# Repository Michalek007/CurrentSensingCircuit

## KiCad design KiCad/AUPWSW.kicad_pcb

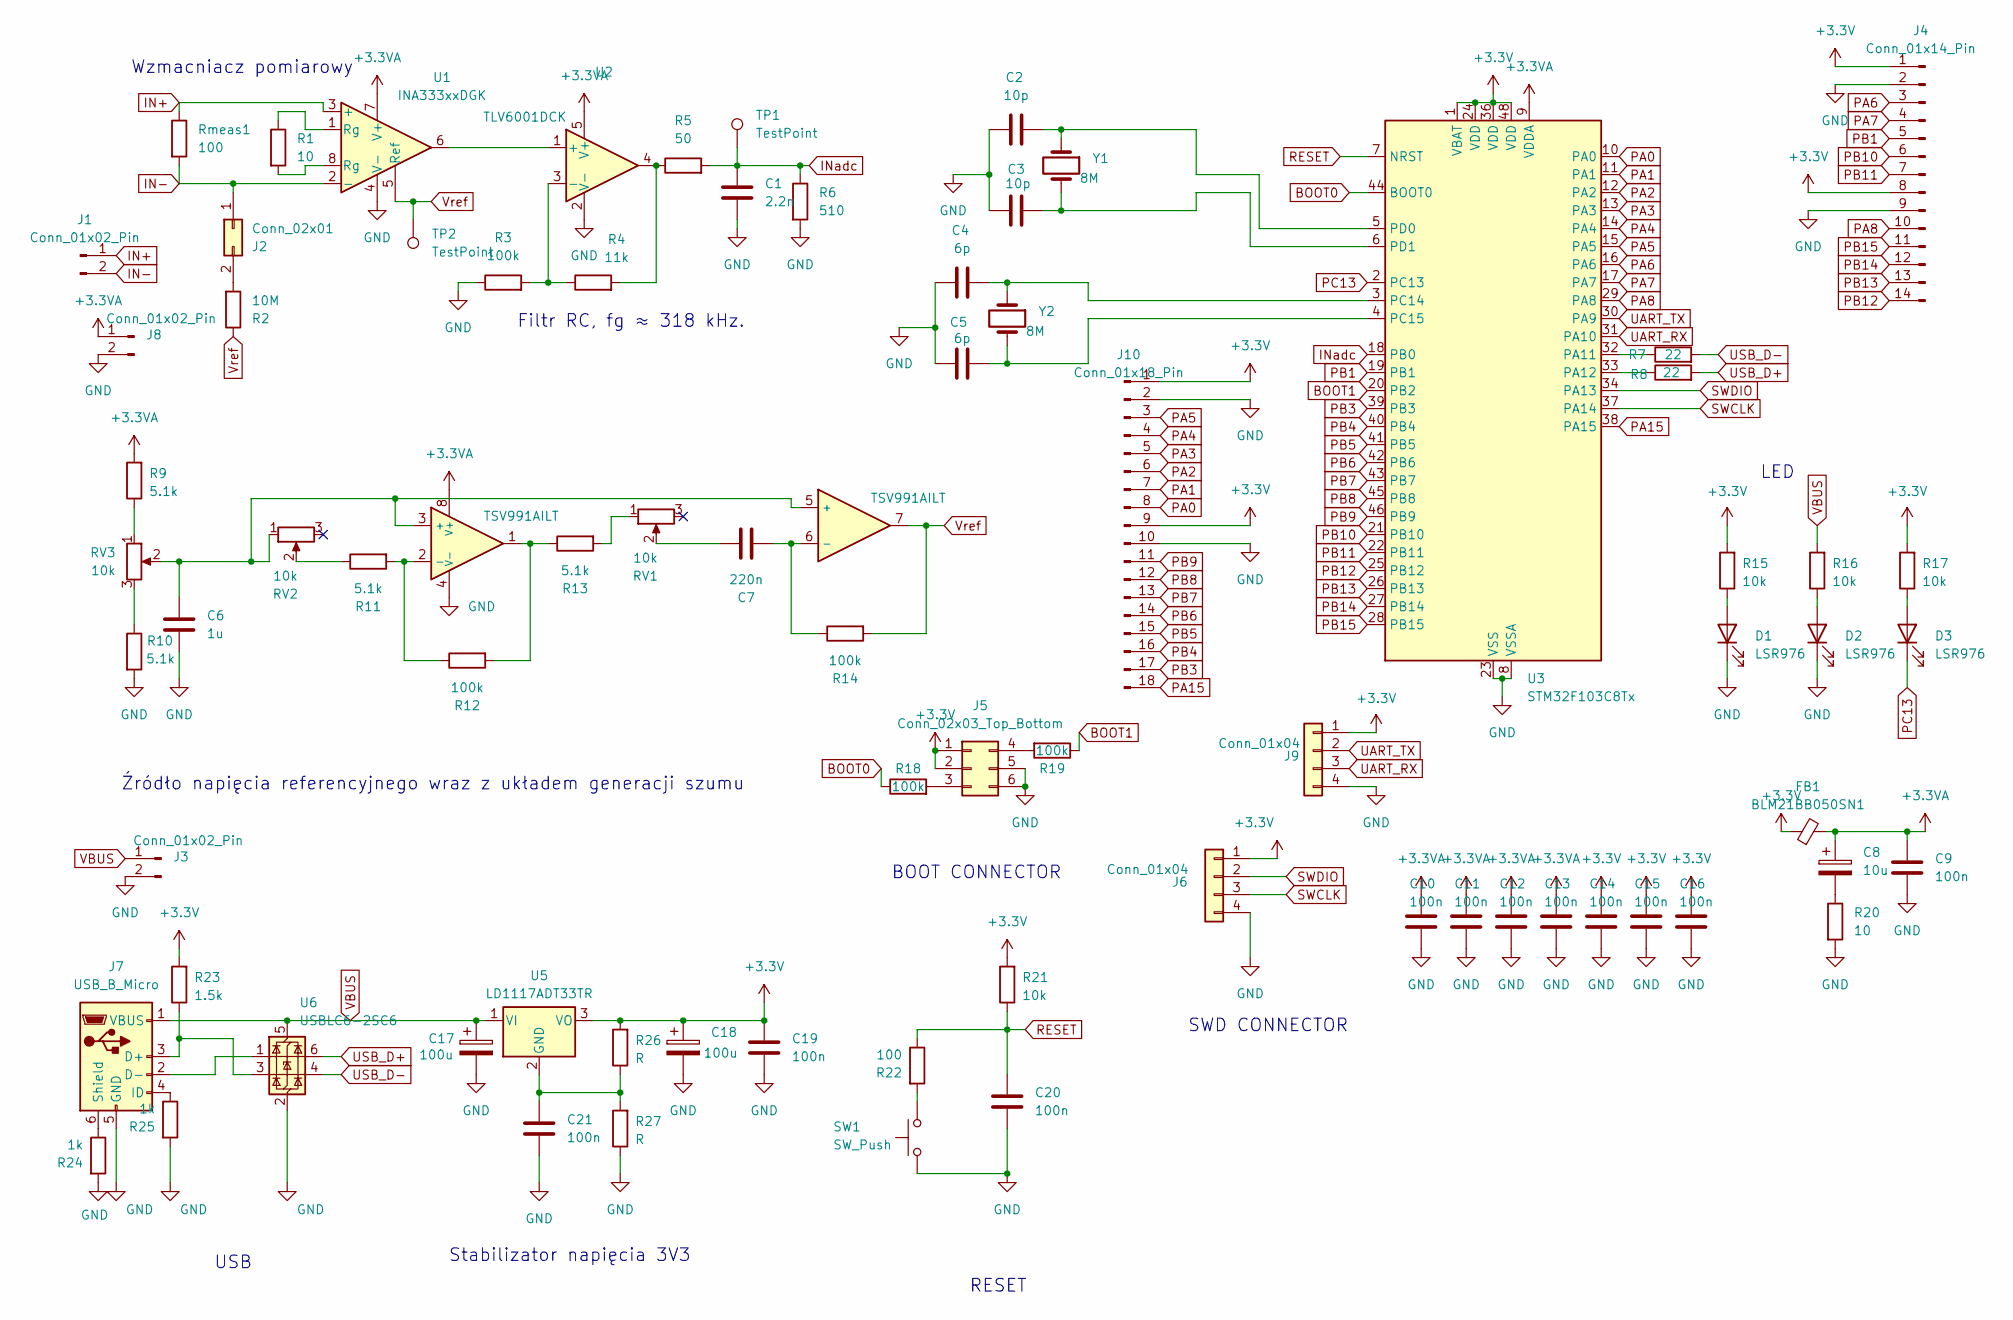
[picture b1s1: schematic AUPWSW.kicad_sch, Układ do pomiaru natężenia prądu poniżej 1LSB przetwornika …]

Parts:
C1: 2.2n; C_0805_2012Metric_Pad1.18x1.45mm_HandSolder
C2, C3: 10p; C_0603_1608Metric_Pad1.08x0.95mm_HandSolder
C4, C5: 6p; C_0603_1608Metric_Pad1.08x0.95mm_HandSolder
C6: 1u; C_0805_2012Metric_Pad1.18x1.45mm_HandSolder
C7: 220n; C_0805_2012Metric_Pad1.18x1.45mm_HandSolder
C8: 10u; CP_Elec_5x3
C9, C10, C11, C12, C13, C14, C15, C16, C19, C20, C21: 100n; C_0805_2012Metric_Pad1.18x1.45mm_HandSolder
C17, C18: 100u; CP_Elec_6.3x3
D1, D2, D3: LSR976; LED_0805_2012Metric_Pad1.15x1.40mm_HandSolder
FB1: BLM21BB050SN1; R_0805_2012Metric_Pad1.20x1.40mm_HandSolder
J1, J3, J8: Conn_01x02_Pin; PinHeader_1x02_P2.54mm_Vertical
J2: Conn_02x01; PinHeader_1x02_P2.54mm_Vertical
J4: Conn_01x14_Pin; PinHeader_1x14_P2.54mm_Vertical
J5: Conn_02x03_Top_Bottom; PinHeader_2x03_P2.54mm_Vertical
J6, J9: Conn_01x04; PinHeader_1x04_P2.54mm_Vertical
J7: USB_B_Micro; USB3080-30-00-A
J10: Conn_01x18_Pin; PinHeader_1x18_P2.54mm_Vertical
R1, R20: 10; R_0805_2012Metric_Pad1.20x1.40mm_HandSolder
R2: 10M; R_0805_2012Metric_Pad1.20x1.40mm_HandSolder
R3, R12, R14, R18, R19: 100k; R_0805_2012Metric_Pad1.20x1.40mm_HandSolder
R4: 11k; R_0805_2012Metric_Pad1.20x1.40mm_HandSolder
R5: 50; R_0805_2012Metric_Pad1.20x1.40mm_HandSolder
R6: 510; R_0805_2012Metric_Pad1.20x1.40mm_HandSolder
R7, R8: 22; R_0805_2012Metric_Pad1.20x1.40mm_HandSolder
R9, R10, R11, R13: 5.1k; R_0805_2012Metric_Pad1.20x1.40mm_HandSolder
R15, R16, R17, R21: 10k; R_0805_2012Metric_Pad1.20x1.40mm_HandSolder
R22: 100; R_0805_2012Metric_Pad1.20x1.40mm_HandSolder
R23: 1.5k; R_0805_2012Metric_Pad1.20x1.40mm_HandSolder
R24, R25: 1k; R_0805_2012Metric_Pad1.20x1.40mm_HandSolder
R26, R27: R; R_0805_2012Metric_Pad1.20x1.40mm_HandSolder
RV1, RV2, RV3: 10k; 1806WSMD
Rmeas1: 100; R_0805_2012Metric_Pad1.20x1.40mm_HandSolder
SW1: SW_Push; TL3305BF160QG
TP1, TP2: TestPoint; TestPoint_THTPad_1.5x1.5mm_Drill0.7mm
U1: INA333xxDGK; VSSOP-8_3x3mm_P0.65mm
U2: TLV6001DCK; SOT-353_SC-70-5
U3: STM32F103C8Tx; LQFP-48_7x7mm_P0.5mm
U4: TSV991AILT; SOIC127P600X175-8N
U5: LD1117ADT33TR; TO228P972X240-3N
U6: USBLC6-2SC6; SOT-23-6
Y1: 8M; HC49SSDLF800MHZ
Y2: 8M; ABS2532768KHZT

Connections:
+3.3V: C14.1, C15.1, C16.1, C18.1, C19.1, FB1.1, J4.1, J4.8, J5.1, J5.2, J6.1, J9.1, J10.1, J10.9, R15.2, R17.2, R21.2, R23.2, R26.2, U3.1 (VBAT), U3.24 (VDD), U3.36 (VDD), U3.48 (VDD), U5.3 (VO)
+3.3VA: C8.1, C9.1, C10.1, C11.1, C12.1, C13.1, FB1.2, J8.1, R9.2, U1.7 (V+), U2.5 (V+), U3.9 (VDDA), U4.8 (V+)
BOOT0: R18.1, U3.44 (BOOT0)
BOOT1: R19.1, U3.20 (PB2)
GND: C1.2, C2.2, C3.2, C4.2, C5.2, C6.2, C9.2, C10.2, C11.2, C12.2, C13.2, C14.2, C15.2, C16.2, C17.2, C18.2, C19.2, C20.2, C21.2, D1.1 (K), D2.1 (K), J3.2, J4.2, J4.9, J5.5, J5.6, J6.4, J7.5 (GND), J8.2, J9.4, J10.2, J10.10, R3.1, R6.2, R10.2, R20.2, R24.2, R25.2, R27.1, SW1.1, U1.4 (V-), U2.2 (V-), U3.8 (VSSA), U3.23 (VSS), U3.35 (VSS), U3.47 (VSS), U4.4 (V-), U6.2 (GND)
IN+: J1.1, Rmeas1.1, U1.3 (+)
IN-: J1.2, J2.1, Rmeas1.2, U1.2 (-)
INadc: C1.1, R5.2, R6.1, TP1.1, U3.18 (PB0)
unnamed: C7.1, RV1.2
unnamed: C8.2, R20.1
unnamed: D1.2 (A), R15.1
unnamed: D2.2 (A), R16.1
unnamed: D3.2 (A), R17.1
unnamed: J2.2, R2.2
unnamed: J5.3, R18.2
unnamed: J5.4, R19.2
unnamed: J7.3 (D+), R23.1, U6.3 (I/O2)
unnamed: J7.2 (D-), U6.1 (I/O1)
unnamed: J7.4 (ID), R25.1
unnamed: J7.6 (Shield), R24.1
unnamed: R1.1, U1.1 (Rg)
unnamed: R1.2, U1.8 (Rg)
unnamed: R4.2, R5.1, U2.4
unnamed: R9.1, RV3.1
unnamed: R10.1, RV3.3
unnamed: R11.1, RV2.2
unnamed: R12.2, R13.1, U4.1
unnamed: R13.2, RV1.1
unnamed: R22.2, SW1.2
unnamed: U1.6, U2.1 (+)
unnamed: R3.2, R4.1, U2.3 (-)
unnamed: R7.1, U3.32 (PA11)
unnamed: R8.1, U3.33 (PA12)
unnamed: C4.1, U3.3 (PC14), Y2.1
unnamed: C5.1, U3.4 (PC15), Y2.2
unnamed: C2.1, U3.5 (PD0), Y1.1
unnamed: C3.1, U3.6 (PD1), Y1.2
unnamed: C6.1, RV2.1, RV3.2, U4.3 (+), U4.5 (+)
unnamed: R11.2, R12.1, U4.2 (-)
unnamed: C7.2, R14.1, U4.6 (-)
unnamed: C21.1, R26.1, R27.2, U5.2 (GND)
PA0: J10.8, U3.10 (PA0)
PA1: J10.7, U3.11 (PA1)
PA2: J10.6, U3.12 (PA2)
PA3: J10.5, U3.13 (PA3)
PA4: J10.4, U3.14 (PA4)
PA5: J10.3, U3.15 (PA5)
PA6: J4.3, U3.16 (PA6)
PA7: J4.4, U3.17 (PA7)
PA8: J4.10, U3.29 (PA8)
PA15: J10.18, U3.38 (PA15)
PB1: J4.5, U3.19 (PB1)
PB3: J10.17, U3.39 (PB3)
PB4: J10.16, U3.40 (PB4)
PB5: J10.15, U3.41 (PB5)
PB6: J10.14, U3.42 (PB6)
PB7: J10.13, U3.43 (PB7)
PB8: J10.12, U3.45 (PB8)
PB9: J10.11, U3.46 (PB9)
PB10: J4.6, U3.21 (PB10)
PB11: J4.7, U3.22 (PB11)
PB12: J4.14, U3.25 (PB12)
PB13: J4.13, U3.26 (PB13)
PB14: J4.12, U3.27 (PB14)
PB15: J4.11, U3.28 (PB15)
PC13: D3.1 (K), U3.2 (PC13)
RESET: C20.1, R21.1, R22.1, U3.7 (NRST)
SWCLK: J6.3, U3.37 (PA14)
SWDIO: J6.2, U3.34 (PA13)
UART_RX: J9.3, U3.31 (PA10)
UART_TX: J9.2, U3.30 (PA9)
USB_D+: R8.2, U6.6 (I/O1)
USB_D-: R7.2, U6.4 (I/O2)
VBUS: C17.1, J3.1, J7.1 (VBUS), R16.2, U5.1 (VI), U6.5 (VBUS)
Vref: R2.1, R14.2, TP2.1, U1.5 (Ref), U4.7

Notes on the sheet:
Źródło napięcia referencyjnego wraz z układem generacji szumu
Wzmacniacz pomiarowy
RESET
Stabilizator napięcia 3V3
USB
SWD CONNECTOR
BOOT CONNECTOR
LED
Filtr RC, fg ≈ 318 kHz.

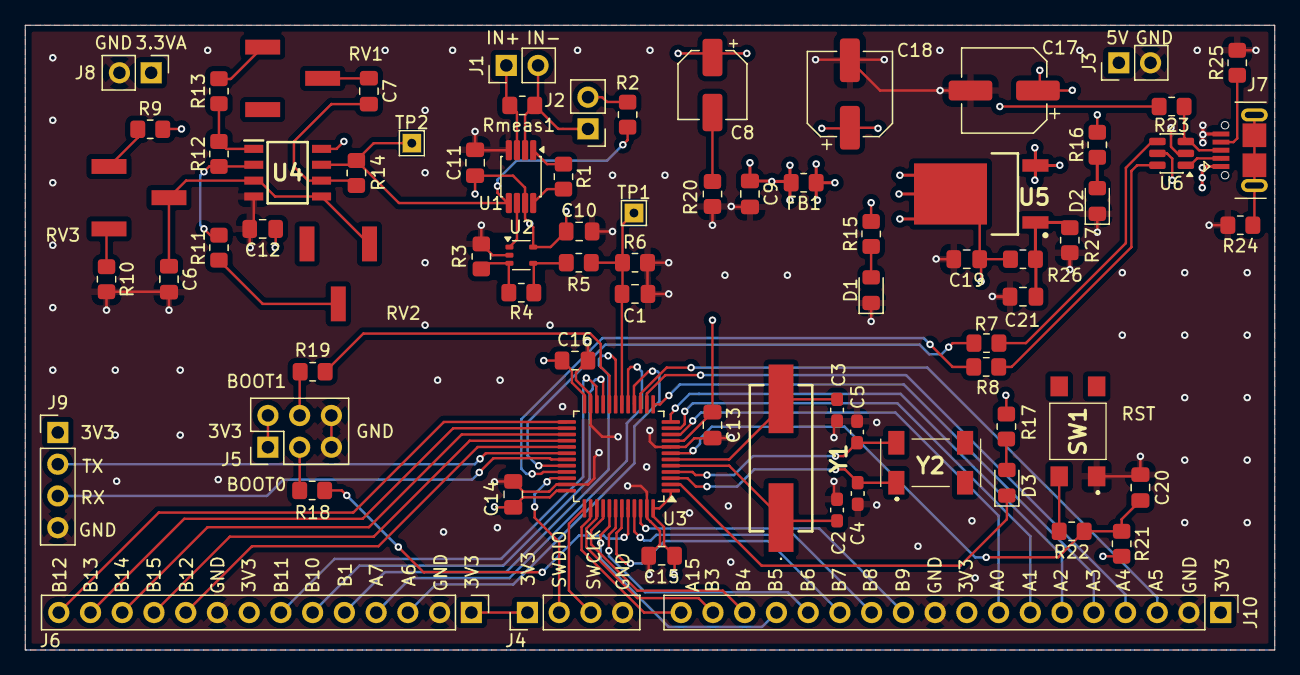
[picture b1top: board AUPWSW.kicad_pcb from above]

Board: 4 copper layers, 100.0 x 50.0 mm, 77 parts (0 on the bottom side), 75 nets.

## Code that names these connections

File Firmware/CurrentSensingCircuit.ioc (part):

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Mcu.Name=STM32F103C(8-B)Tx
Mcu.Package=LQFP48
Mcu.UserName=STM32F103C8Tx
PA10.Mode=Asynchronous
PA10.Signal=USART1_RX
PA9.Mode=Asynchronous
PA9.Signal=USART1_TX
PB0.Signal=ADCx_IN8
PD0-OSC_IN.Mode=HSE-External-Oscillator
PD0-OSC_IN.Signal=RCC_OSC_IN
PD1-OSC_OUT.Mode=HSE-External-Oscillator
PD1-OSC_OUT.Signal=RCC_OSC_OUT
RCC.SYSCLKFreq_VALUE=72000000
RCC.SYSCLKSource=RCC_SYSCLKSOURCE_PLLCLK
board=custom

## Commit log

2025-10-20 Schemat blokowy + zalozenia
2025-10-20 added datasheets
2025-10-21 added LPF and labels
2025-10-26 added .pdf to gitignore
2025-10-27 Added: simulations (psu + sumator)
2025-10-27 added INA333 and LM336 simulations
2025-10-27 Added: schematic of PSU
2025-10-27 doc update
2025-11-04 Noise generation update
2025-11-11 schematics and doc update
2025-11-11 Add KiCad files
    TEST
2025-11-11 added missing datasheets
2025-11-11 KICAD update
2025-11-11 deleted unneeded files
2025-11-15 schematic update
    pending for team review
2025-11-16 added some comments to schematic
2025-11-17 Added comments to schematic
2025-11-17 schematic update
    team review
2025-11-17 added LPF sim
2025-11-24 Schematic update
2025-11-24 tsv992 footprint
2025-11-24 ferrite simulation and schematic update
2025-11-25 Updated schematic, added footprints and custom lib
2025-11-25 added missing datasheets and JLCPCB design rules
2025-11-25 led doc update
2025-11-27 Updated PCB layout
2025-11-29 Arranged components on PCB
2025-11-29 Updated: pcb and schematic
2025-11-30 Updated: D+ and D- routing
2025-12-01 Added pins names on silkscreen layer
2025-12-05 Updated pcb: added VBUS plane and more connectors + modified USB routing (D+ and D-)
2025-12-06 Added gnd pours on top and bottom layers
2025-12-07 PCB routing update, moved LSE to top layer
2025-12-08 PCB final
2025-12-08 Added gerbers
2025-12-16 added BOM and links to shops
2026-01-28 Added firmware - initial setup
2026-02-08 Updated: firmware, added: UART reading data in python
2026-02-08 Added plotting results in python
2026-02-11 Added: calibration of ADC, filtering signal with FIR in python
2026-02-12 Added images for report
2026-02-13 added report template
2026-02-18 added report
2026-02-19 updated report
